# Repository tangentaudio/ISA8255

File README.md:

# ISA8255
ISA bus 8255 I/O card, a 2024 layout of a hand-wired design that I made in the early 1990s for robotics projects.

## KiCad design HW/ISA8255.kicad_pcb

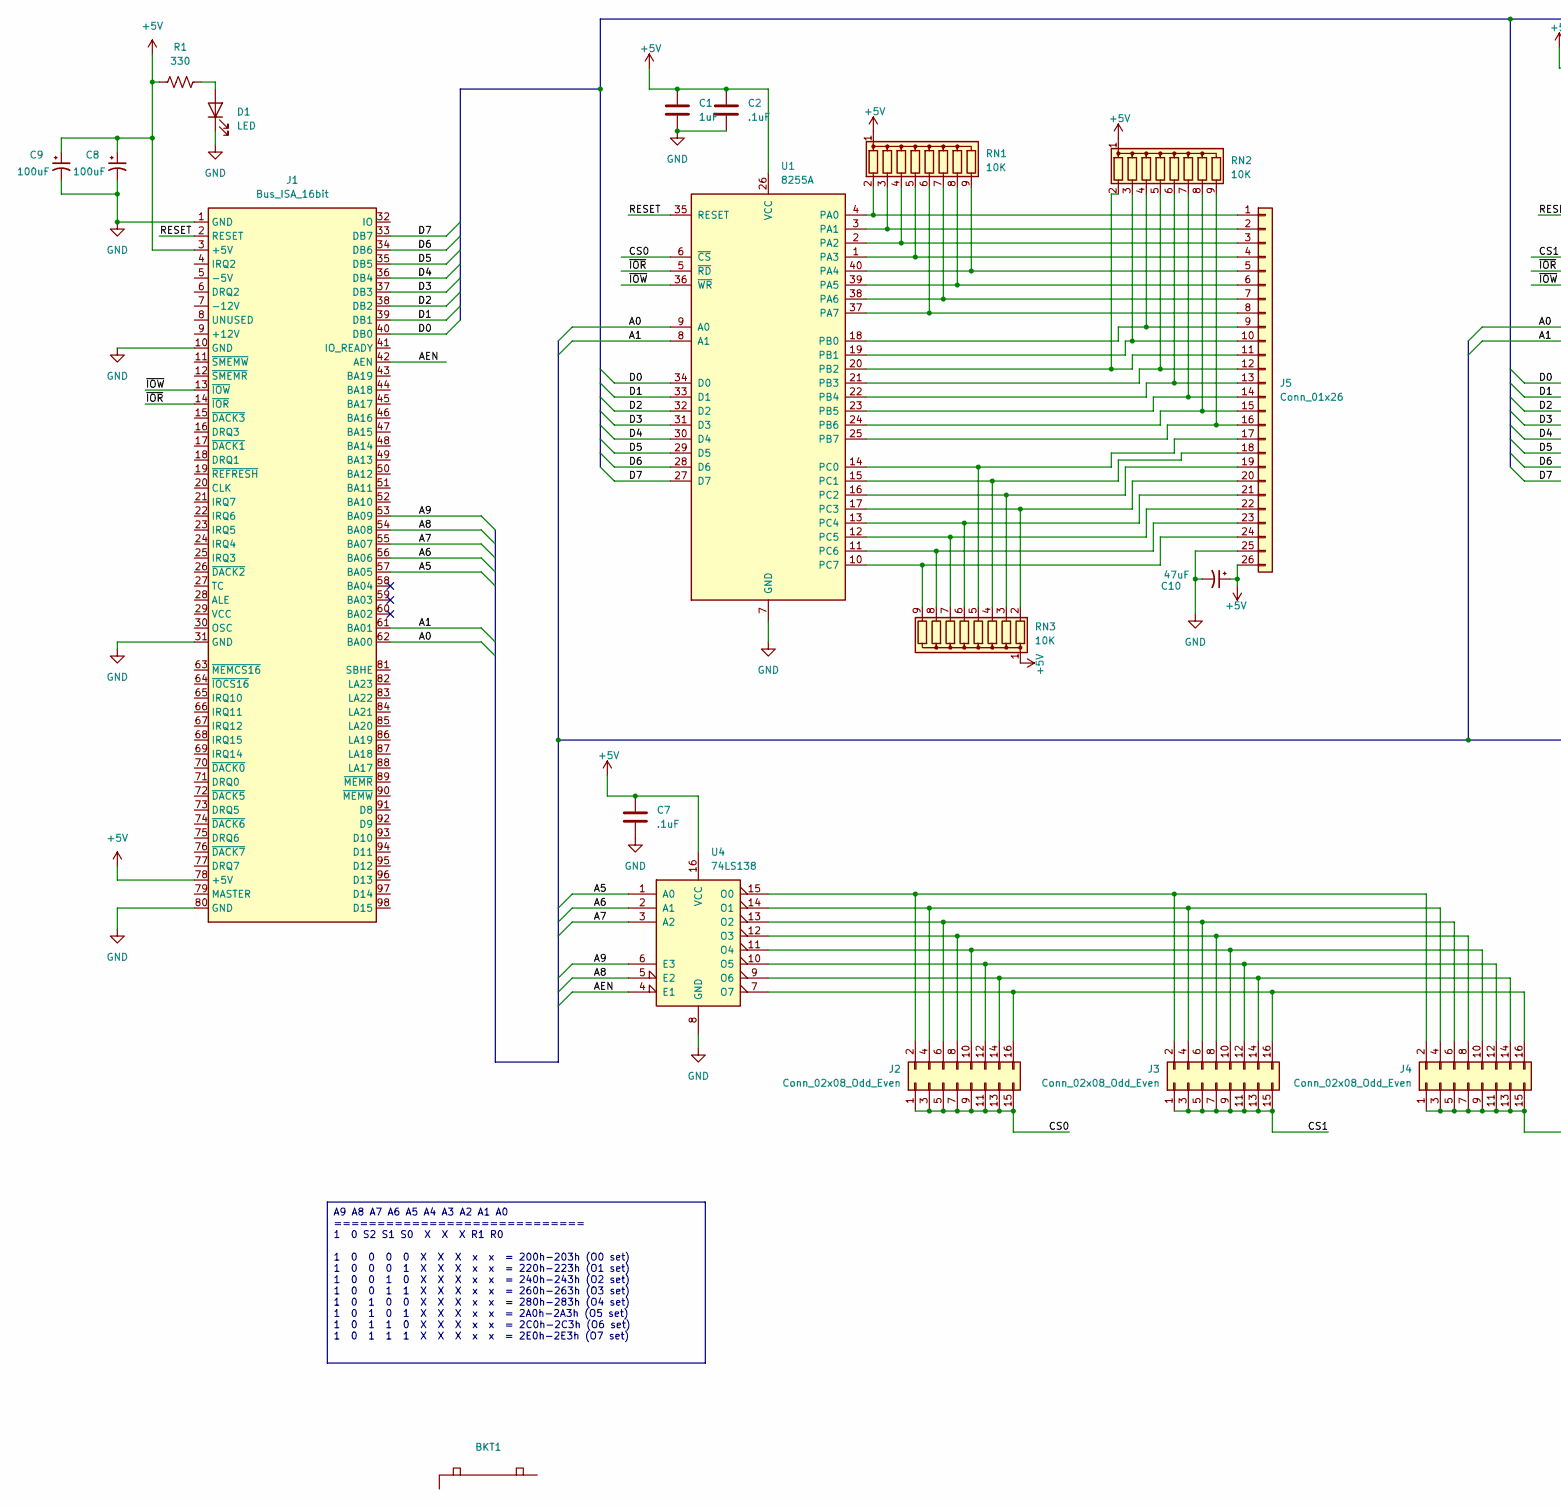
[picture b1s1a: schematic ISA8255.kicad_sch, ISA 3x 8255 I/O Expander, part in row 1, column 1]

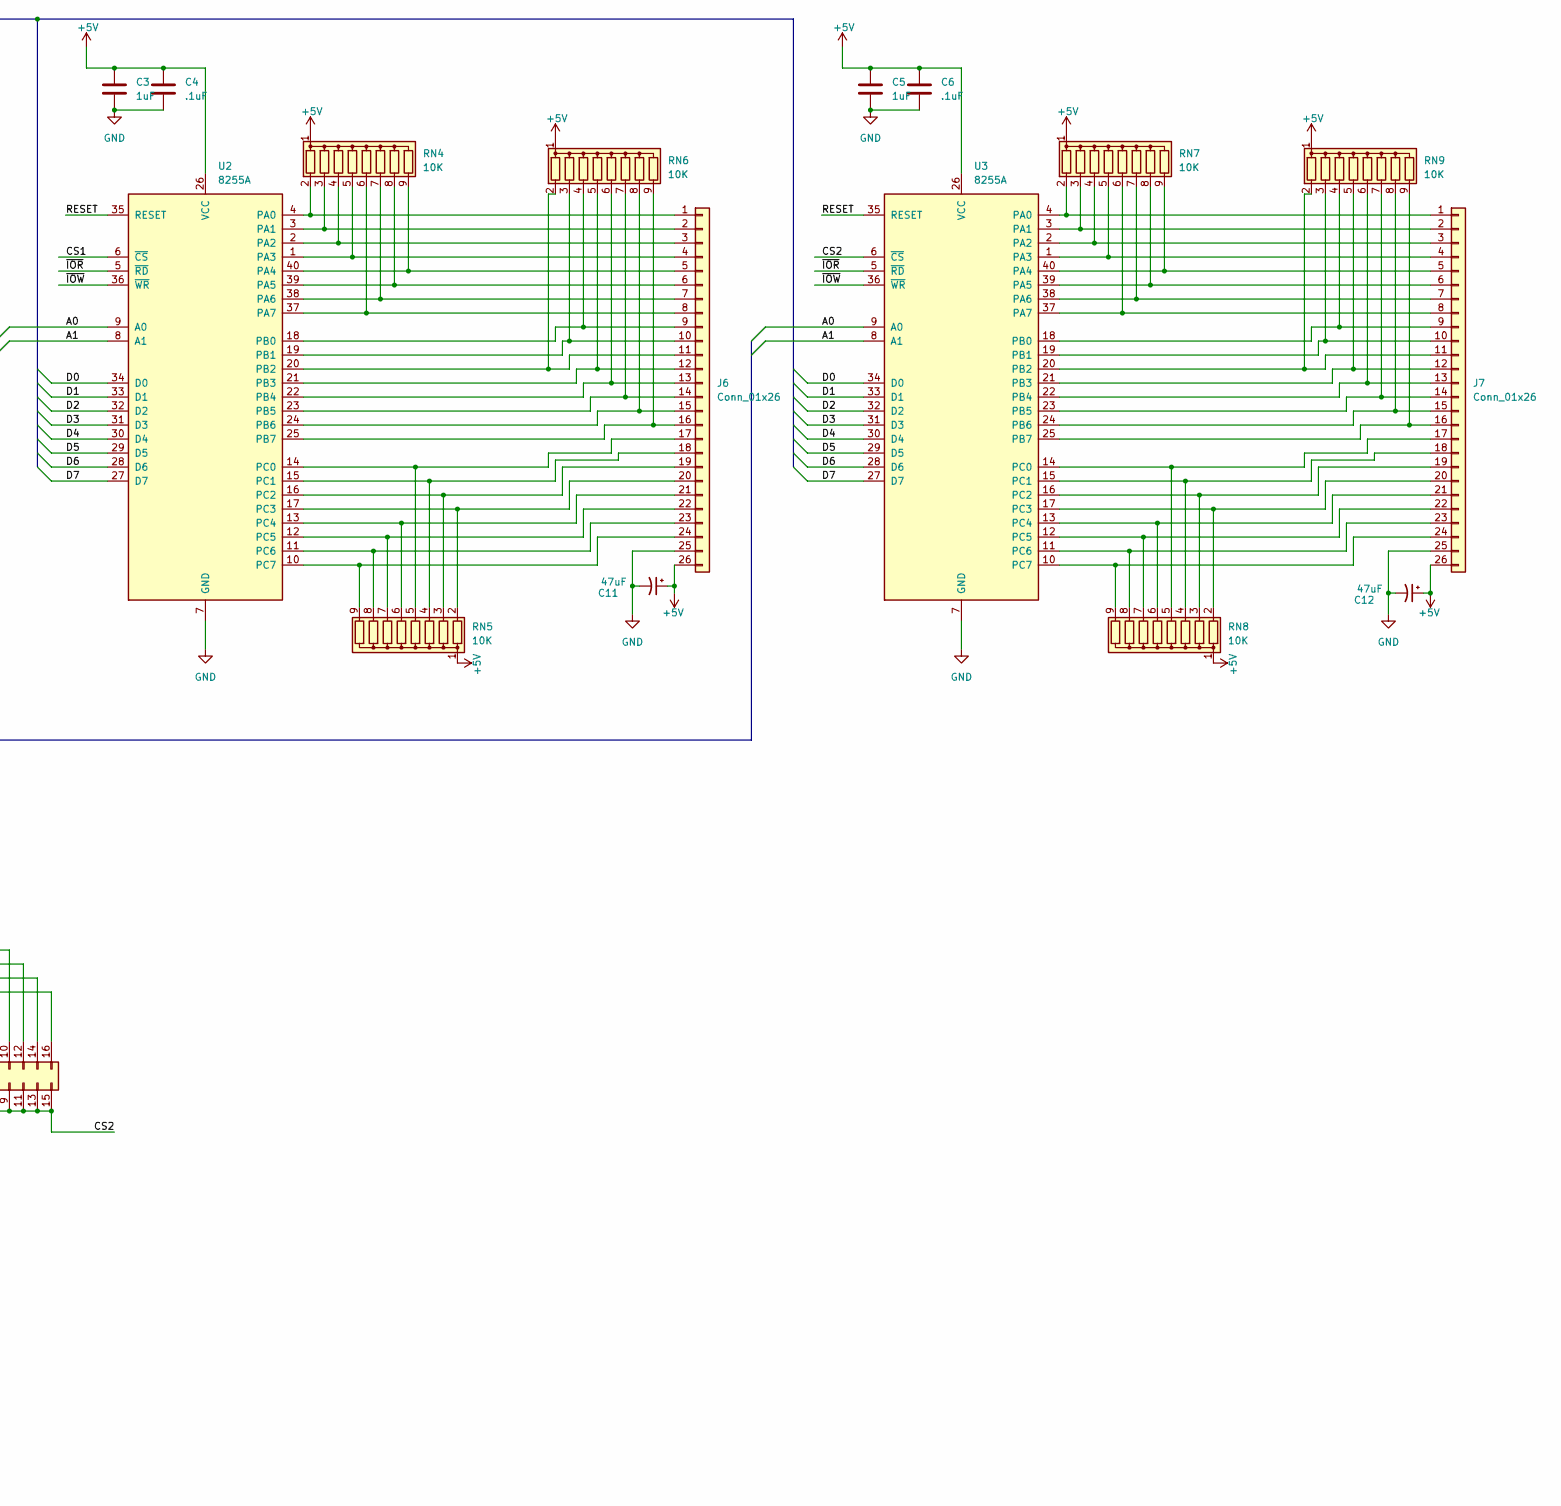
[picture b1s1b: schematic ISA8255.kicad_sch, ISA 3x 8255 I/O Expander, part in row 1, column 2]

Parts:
BKT1: KEYSTONE-9202
C1, C3, C5: 1uF; C_Disc_D5.0mm_W2.5mm_P5.00mm
C2, C4, C6, C7: .1uF; C_Disc_D5.0mm_W2.5mm_P5.00mm
C8, C9: 100uF; CP_Radial_D8.0mm_P2.50mm
C10, C11, C12: 47uF; CP_Radial_D6.3mm_P2.50mm
D1: LED; LED_D5.0mm
J1: Bus_ISA_16bit; BUS_AT
J2, J3, J4: Conn_02x08_Odd_Even; PinHeader_2x08_P2.54mm_Vertical
J5, J6, J7: Conn_01x26; IDC-Header_2x13_P2.54mm_Horizontal
R1: 330; R_Axial_DIN0207_L6.3mm_D2.5mm_P7.62mm_Horizontal
RN1, RN2, RN3, RN4, RN5, RN6, RN7, RN8, RN9: 10K; R_Array_SIP9
U1, U2, U3: 8255A; DIP-40_W15.24mm
U4: 74LS138; DIP-16_W7.62mm

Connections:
+5V: C1.1, C2.1, C3.1, C4.1, C5.1, C6.1, C7.1, C8.1, C9.1, C10.1, C11.1, C12.1, J1.3 (+5V), J1.78 (+5V), J5.26, J6.26, J7.26, R1.1, RN1.1 (common), RN2.1 (common), RN3.1 (common), RN4.1 (common), RN5.1 (common), RN6.1 (common), RN7.1 (common), RN8.1 (common), RN9.1 (common), U1.26 (VCC), U2.26 (VCC), U3.26 (VCC), U4.16 (VCC)
/A0: J1.62 (BA00), U1.9 (A0), U2.9 (A0), U3.9 (A0)
/A1: J1.61 (BA01), U1.8 (A1), U2.8 (A1), U3.8 (A1)
/A5: J1.57 (BA05), U4.1 (A0)
/A6: J1.56 (BA06), U4.2 (A1)
/A7: J1.55 (BA07), U4.3 (A2)
/A8: J1.54 (BA08), U4.5 (E2)
/A9: J1.53 (BA09), U4.6 (E3)
/AEN: J1.42 (AEN), U4.4 (E1)
/CS0: J2.1, J2.3, J2.5, J2.7, J2.9, J2.11, J2.13, J2.15, U1.6 (~CS)
/CS1: J3.1, J3.3, J3.5, J3.7, J3.9, J3.11, J3.13, J3.15, U2.6 (~CS)
/CS2: J4.1, J4.3, J4.5, J4.7, J4.9, J4.11, J4.13, J4.15, U3.6 (~CS)
/D0: J1.40 (DB0), U1.34 (D0), U2.34 (D0), U3.34 (D0)
/D1: J1.39 (DB1), U1.33 (D1), U2.33 (D1), U3.33 (D1)
/D2: J1.38 (DB2), U1.32 (D2), U2.32 (D2), U3.32 (D2)
/D3: J1.37 (DB3), U1.31 (D3), U2.31 (D3), U3.31 (D3)
/D4: J1.36 (DB4), U1.30 (D4), U2.30 (D4), U3.30 (D4)
/D5: J1.35 (DB5), U1.29 (D5), U2.29 (D5), U3.29 (D5)
/D6: J1.34 (DB6), U1.28 (D6), U2.28 (D6), U3.28 (D6)
/D7: J1.33 (DB7), U1.27 (D7), U2.27 (D7), U3.27 (D7)
/RESET: J1.2 (RESET), U1.35 (RESET), U2.35 (RESET), U3.35 (RESET)
/~IOR: J1.14 (~IOR), U1.5 (~RD), U2.5 (~RD), U3.5 (~RD)
/~IOW: J1.13 (~IOW), U1.36 (~WR), U2.36 (~WR), U3.36 (~WR)
GND: C1.2, C2.2, C3.2, C4.2, C5.2, C6.2, C7.2, C8.2, C9.2, C10.2, C11.2, C12.2, D1.1 (K), J1.1 (GND), J1.10 (GND), J1.31 (GND), J1.80 (GND), J5.25, J6.25, J7.25, U1.7 (GND), U2.7 (GND), U3.7 (GND), U4.8 (GND)
unnamed: D1.2 (A), R1.2
unnamed: J2.2, J3.2, J4.2, U4.15 (O0)
unnamed: J2.4, J3.4, J4.4, U4.14 (O1)
unnamed: J2.6, J3.6, J4.6, U4.13 (O2)
unnamed: J2.8, J3.8, J4.8, U4.12 (O3)
unnamed: J2.10, J3.10, J4.10, U4.11 (O4)
unnamed: J2.12, J3.12, J4.12, U4.10 (O5)
unnamed: J2.14, J3.14, J4.14, U4.9 (O6)
unnamed: J2.16, J3.16, J4.16, U4.7 (O7)
unnamed: J5.1, RN1.2 (R1), U1.4 (PA0)
unnamed: J5.2, RN1.3 (R2), U1.3 (PA1)
unnamed: J5.3, RN1.4 (R3), U1.2 (PA2)
unnamed: J5.4, RN1.5 (R4), U1.1 (PA3)
unnamed: J5.5, RN1.9 (R8), U1.40 (PA4)
unnamed: J5.6, RN1.8 (R7), U1.39 (PA5)
unnamed: J5.7, RN1.7 (R6), U1.38 (PA6)
unnamed: J5.8, RN1.6 (R5), U1.37 (PA7)
unnamed: J5.9, RN2.4 (R3), U1.18 (PB0)
unnamed: J5.10, RN2.3 (R2), U1.19 (PB1)
unnamed: J5.11, RN2.2 (R1), U1.20 (PB2)
unnamed: J5.12, RN2.5 (R4), U1.21 (PB3)
unnamed: J5.13, RN2.6 (R5), U1.22 (PB4)
unnamed: J5.14, RN2.7 (R6), U1.23 (PB5)
unnamed: J5.15, RN2.8 (R7), U1.24 (PB6)
unnamed: J5.16, RN2.9 (R8), U1.25 (PB7)
unnamed: J5.17, RN3.5 (R4), U1.14 (PC0)
unnamed: J5.18, RN3.4 (R3), U1.15 (PC1)
unnamed: J5.19, RN3.3 (R2), U1.16 (PC2)
unnamed: J5.20, RN3.2 (R1), U1.17 (PC3)
unnamed: J5.21, RN3.6 (R5), U1.13 (PC4)
unnamed: J5.22, RN3.7 (R6), U1.12 (PC5)
unnamed: J5.23, RN3.8 (R7), U1.11 (PC6)
unnamed: J5.24, RN3.9 (R8), U1.10 (PC7)
unnamed: J6.1, RN4.2 (R1), U2.4 (PA0)
unnamed: J6.2, RN4.3 (R2), U2.3 (PA1)
unnamed: J6.3, RN4.4 (R3), U2.2 (PA2)
unnamed: J6.4, RN4.5 (R4), U2.1 (PA3)
unnamed: J6.5, RN4.9 (R8), U2.40 (PA4)
unnamed: J6.6, RN4.8 (R7), U2.39 (PA5)
unnamed: J6.7, RN4.7 (R6), U2.38 (PA6)
unnamed: J6.8, RN4.6 (R5), U2.37 (PA7)
unnamed: J6.9, RN6.4 (R3), U2.18 (PB0)
unnamed: J6.10, RN6.3 (R2), U2.19 (PB1)
unnamed: J6.11, RN6.2 (R1), U2.20 (PB2)
unnamed: J6.12, RN6.5 (R4), U2.21 (PB3)
unnamed: J6.13, RN6.6 (R5), U2.22 (PB4)
unnamed: J6.14, RN6.7 (R6), U2.23 (PB5)
unnamed: J6.15, RN6.8 (R7), U2.24 (PB6)
unnamed: J6.16, RN6.9 (R8), U2.25 (PB7)
unnamed: J6.17, RN5.5 (R4), U2.14 (PC0)
unnamed: J6.18, RN5.4 (R3), U2.15 (PC1)
unnamed: J6.19, RN5.3 (R2), U2.16 (PC2)
unnamed: J6.20, RN5.2 (R1), U2.17 (PC3)
unnamed: J6.21, RN5.6 (R5), U2.13 (PC4)
unnamed: J6.22, RN5.7 (R6), U2.12 (PC5)
unnamed: J6.23, RN5.8 (R7), U2.11 (PC6)
unnamed: J6.24, RN5.9 (R8), U2.10 (PC7)
unnamed: J7.1, RN7.2 (R1), U3.4 (PA0)
unnamed: J7.2, RN7.3 (R2), U3.3 (PA1)
unnamed: J7.3, RN7.4 (R3), U3.2 (PA2)
unnamed: J7.4, RN7.5 (R4), U3.1 (PA3)
unnamed: J7.5, RN7.9 (R8), U3.40 (PA4)
unnamed: J7.6, RN7.8 (R7), U3.39 (PA5)
unnamed: J7.7, RN7.7 (R6), U3.38 (PA6)
unnamed: J7.8, RN7.6 (R5), U3.37 (PA7)
unnamed: J7.9, RN9.4 (R3), U3.18 (PB0)
unnamed: J7.10, RN9.3 (R2), U3.19 (PB1)
unnamed: J7.11, RN9.2 (R1), U3.20 (PB2)
unnamed: J7.12, RN9.5 (R4), U3.21 (PB3)
unnamed: J7.13, RN9.6 (R5), U3.22 (PB4)
unnamed: J7.14, RN9.7 (R6), U3.23 (PB5)
unnamed: J7.15, RN9.8 (R7), U3.24 (PB6)
unnamed: J7.16, RN9.9 (R8), U3.25 (PB7)
unnamed: J7.17, RN8.5 (R4), U3.14 (PC0)
unnamed: J7.18, RN8.4 (R3), U3.15 (PC1)
unnamed: J7.19, RN8.3 (R2), U3.16 (PC2)
unnamed: J7.20, RN8.2 (R1), U3.17 (PC3)
unnamed: J7.21, RN8.6 (R5), U3.13 (PC4)
unnamed: J7.22, RN8.7 (R6), U3.12 (PC5)
unnamed: J7.23, RN8.8 (R7), U3.11 (PC6)
unnamed: J7.24, RN8.9 (R8), U3.10 (PC7)

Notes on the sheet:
A9 A8 A7 A6 A5 A4 A3 A2 A1 A0 ============================= 1 0 S2 S1 S0 X X X R1 R0 1 0 0 0 0 X X X x x = 200h-203h (O0 set) 1 0 0 0 1 X X X x x = 220h-223h (O1 set) 1 0 0 1 0 X X X x x = 240h-243h (O2 set) 1 0 0 1 1 X X X x x = 260h-263h (O3 set) 1 0 1 0 0 X X X x x = 280h-283h (O4 set) 1 0 1 0 1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

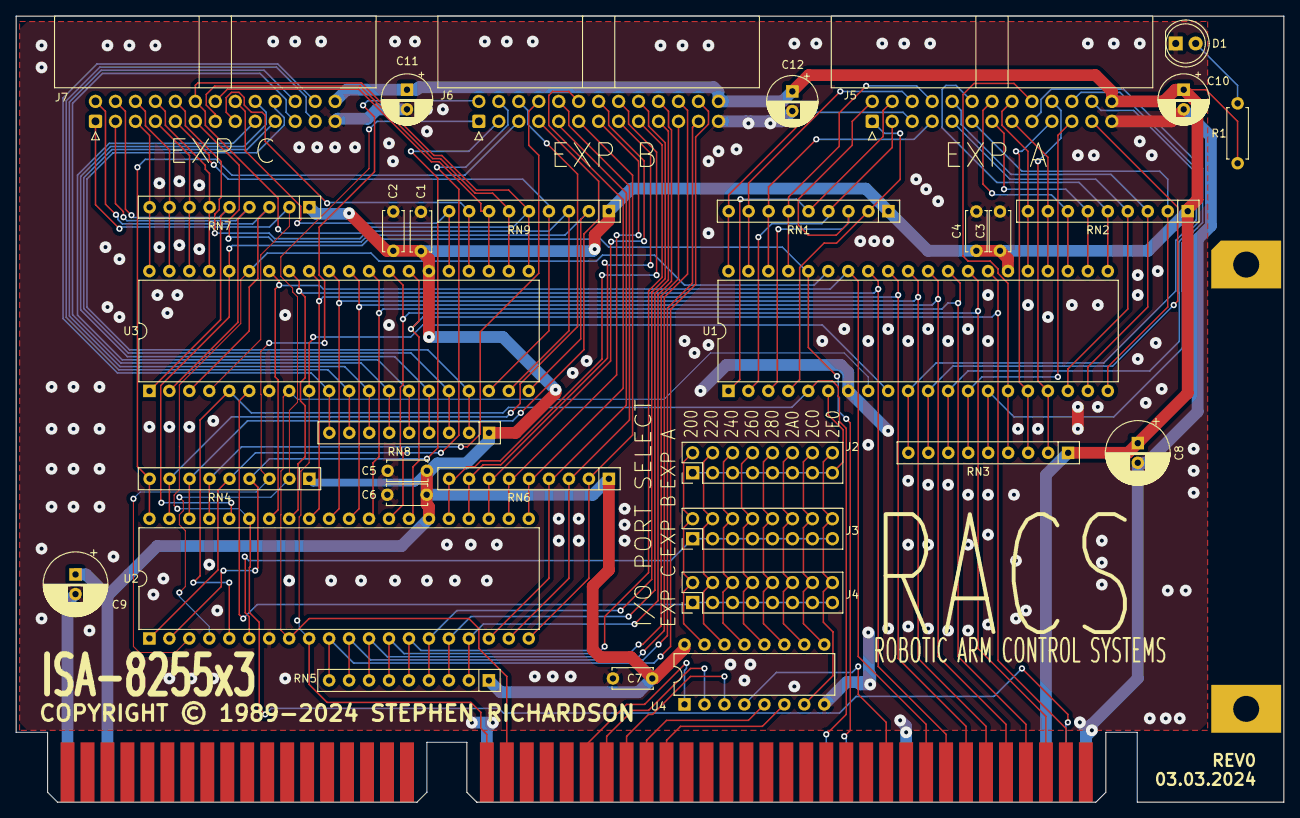
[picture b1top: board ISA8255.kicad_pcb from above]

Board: 2 copper layers, 161.3 x 100.0 mm, 35 parts (0 on the bottom side), 105 nets.

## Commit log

2024-03-03 initial import
2024-03-03 add image
2024-03-03 add handwired photo

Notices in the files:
HW/ISA8255.kicad_pcb:
COPYRIGHT © 1989-2024 STEPHEN RICHARDSON
